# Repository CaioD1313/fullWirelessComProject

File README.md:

# fullWirelessComProject
Schematics, PCB, Firmwares, DataSheets, Notes and Documentation of this project.

# Full Wireless Communication Device

This project was developed as part of the interview process for the Firmware Engineer position. The objective was to build a Full Wireless Communication Device capable of sending data over a 100m air gap. The repository contains the following components in the main folder/root directory:

- **Datasheets**: This folder contains the datasheets used for the development of the project.
- **Schematics and PCB files**: The "KiCad Projeto Tractian" folder includes the schematics and PCB files related to the project.
- **Firmware**: The "Firmware_fullWirelessSystem" folder contains the firmware code for the device.
- **Technical Documentation**: The project's complete technical documentation can be found in the root directory as the file "Project's Technical Documentation.pdf".

Feel free to explore the respective folders for more details on each aspect of the project.

**Be aware! The documentation is long and tedious, as every technical document should be. (:**

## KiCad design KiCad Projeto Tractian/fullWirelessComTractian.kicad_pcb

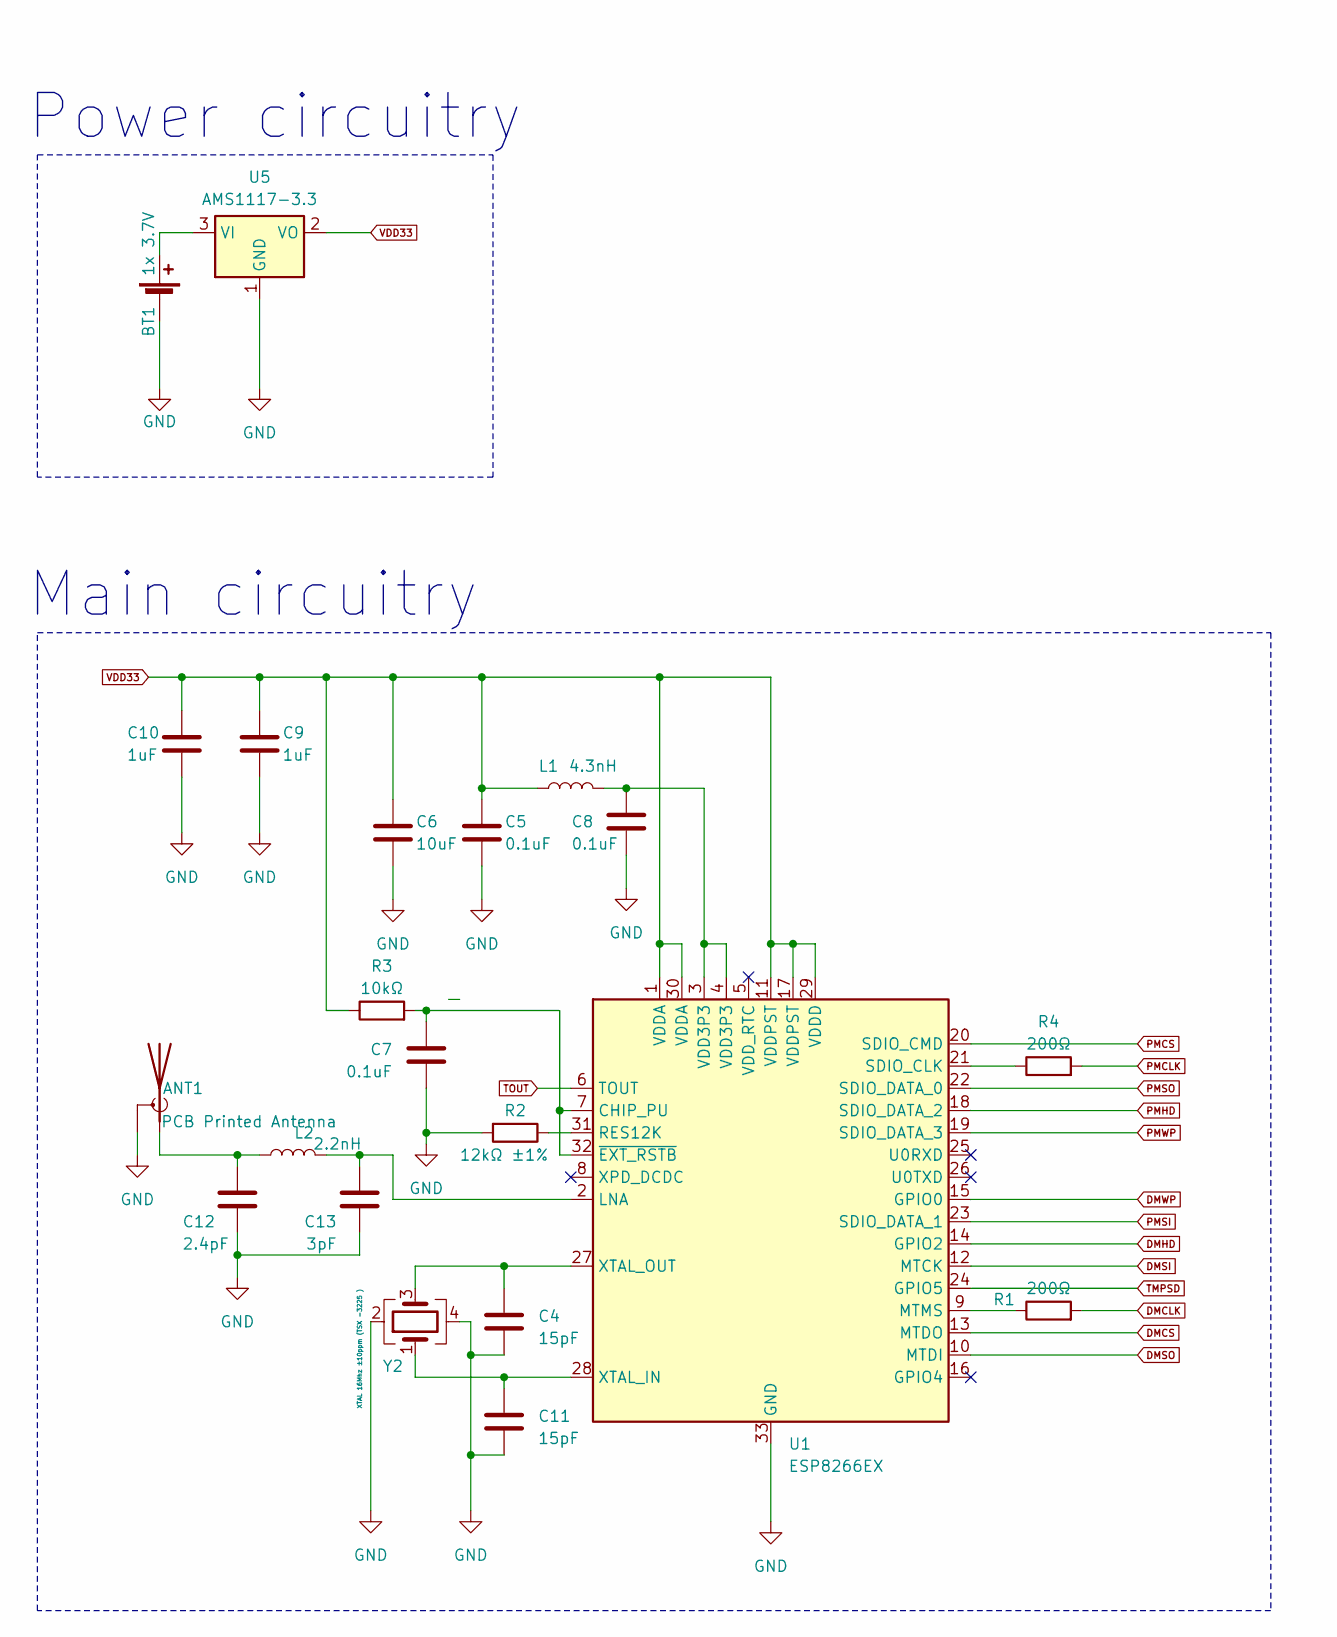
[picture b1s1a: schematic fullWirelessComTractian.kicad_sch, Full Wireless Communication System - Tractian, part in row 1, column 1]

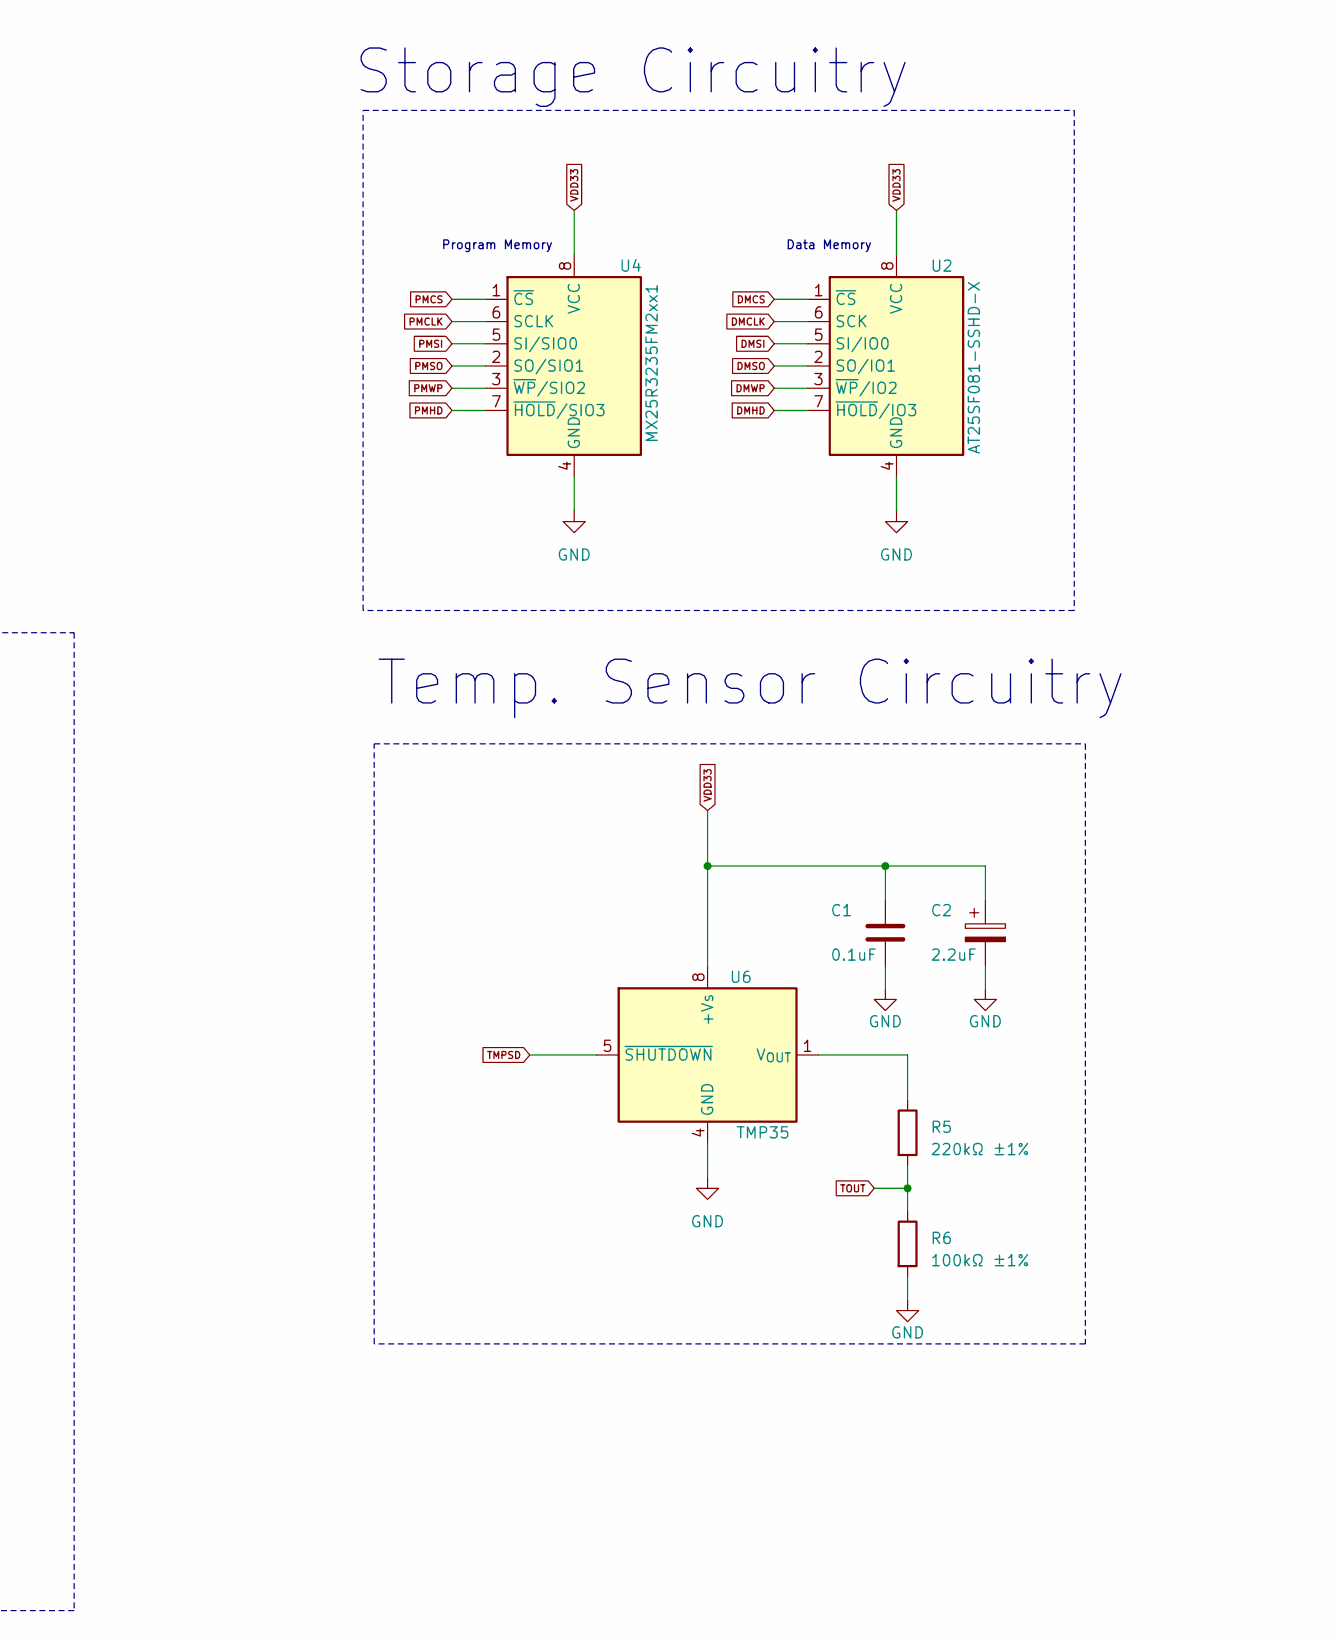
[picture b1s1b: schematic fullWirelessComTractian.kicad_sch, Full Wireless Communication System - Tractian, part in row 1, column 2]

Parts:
ANT1: PCB Printed Antenna; Texas_SWRA117D_2.4GHz_Left
BT1: 1x 3.7V; BatteryHolder_Keystone_2466_1xAAA
C1, C5, C7, C8: 0.1uF; C_0201_0603Metric_Pad0.64x0.40mm_HandSolder
C2: 2.2uF; CP_EIA-1608-08_AVX-J_Pad1.25x1.05mm_HandSolder
C4, C11: 15pF; C_0201_0603Metric_Pad0.64x0.40mm_HandSolder
C6: 10uF; C_0201_0603Metric_Pad0.64x0.40mm_HandSolder
C9, C10: 1uF; C_0201_0603Metric_Pad0.64x0.40mm_HandSolder
C12: 2.4pF; C_0201_0603Metric_Pad0.64x0.40mm_HandSolder
C13: 3pF; C_0201_0603Metric_Pad0.64x0.40mm_HandSolder
L1: 4.3nH; L_0603_1608Metric_Pad1.05x0.95mm_HandSolder
L2: 2.2nH; L_0603_1608Metric_Pad1.05x0.95mm_HandSolder
R1, R4: 200Ω; R_0402_1005Metric_Pad0.72x0.64mm_HandSolder
R2: 12kΩ ±1%; R_0201_0603Metric_Pad0.64x0.40mm_HandSolder
R3: 10kΩ; R_0201_0603Metric_Pad0.64x0.40mm_HandSolder
R5: 220kΩ ±1%; R_0201_0603Metric_Pad0.64x0.40mm_HandSolder
R6: 100kΩ ±1%; R_0201_0603Metric_Pad0.64x0.40mm_HandSolder
U1: ESP8266EX; QFN-32-1EP_5x5mm_P0.5mm_EP3.45x3.45mm
U2: AT25SF081-SSHD-X; SOIC-8_3.9x4.9mm_P1.27mm
U4: MX25R3235FM2xx1; SOP-8_5.28x5.23mm_P1.27mm
U5: AMS1117-3.3; SOT-223-3_TabPin2
U6: TMP35; SOIC-8_3.9x4.9mm_P1.27mm
Y2: XTAL 16Mhz ±10ppm (TSX -3225 ); Oscillator_SMD_SeikoEpson_SG210-4Pin_2.5x2.0mm_HandSoldering

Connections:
DMCLK: R1.2, U2.6 (SCK)
DMCS: U1.13 (MTDO), U2.1 (~CS)
DMHD: U1.14 (GPIO2), U2.7 (~HOLD/IO3)
DMSI: U1.12 (MTCK), U2.5 (SI/IO0)
DMSO: U1.10 (MTDI), U2.2 (SO/IO1)
DMWP: U1.15 (GPIO0), U2.3 (~WP/IO2)
GND: ANT1.2 (Shield), BT1.2 (-), C1.2, C2.2, C4.2, C5.2, C6.2, C7.2, C8.2, C9.2, C10.2, C11.2, C12.2, C13.2, R2.2, R6.2, U1.33 (GND), U2.4 (GND), U4.4 (GND), U5.1 (GND), U6.4 (GND), Y2.2, Y2.4
unnamed: ANT1.1 (A), C12.1, L2.1
unnamed: BT1.1 (+), U5.3 (VI)
unnamed: C8.1, L1.2, U1.3 (VDD3P3), U1.4 (VDD3P3)
unnamed: C7.1, R3.2, U1.7 (CHIP_PU), U1.32 (~EXT_RSTB)
unnamed: C13.1, L2.2, U1.2 (LNA)
unnamed: R1.1, U1.9 (MTMS)
unnamed: R2.1, U1.31 (RES12K)
unnamed: R4.1, U1.21 (SDIO_CLK)
unnamed: C11.1, U1.28 (XTAL_IN), Y2.1
unnamed: C4.1, U1.27 (XTAL_OUT), Y2.3
unnamed: R5.1, U6.1 (V_{OUT})
PMCLK: R4.2, U4.6 (SCLK)
PMCS: U1.20 (SDIO_CMD), U4.1 (~CS)
PMHD: U1.18 (SDIO_DATA_2), U4.7 (~HOLD/SIO3)
PMSI: U1.23 (SDIO_DATA_1), U4.5 (SI/SIO0)
PMSO: U1.22 (SDIO_DATA_0), U4.2 (SO/SIO1)
PMWP: U1.19 (SDIO_DATA_3), U4.3 (~WP/SIO2)
TMPSD: U1.24 (GPIO5), U6.5 (~SHUTDOWN)
TOUT: R5.2, R6.1, U1.6 (TOUT)
VDD33: C1.1, C2.1, C5.1, C6.1, C9.1, C10.1, L1.1, R3.1, U1.1 (VDDA), U1.11 (VDDPST), U1.17 (VDDPST), U1.29 (VDDD), U1.30 (VDDA), U2.8 (VCC), U4.8 (VCC), U5.2 (VO), U6.8 (+Vs)

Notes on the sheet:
Temp. Sensor Circuitry
Storage Circuitry
Program Memory
Data Memory
Main circuitry
Power circuitry

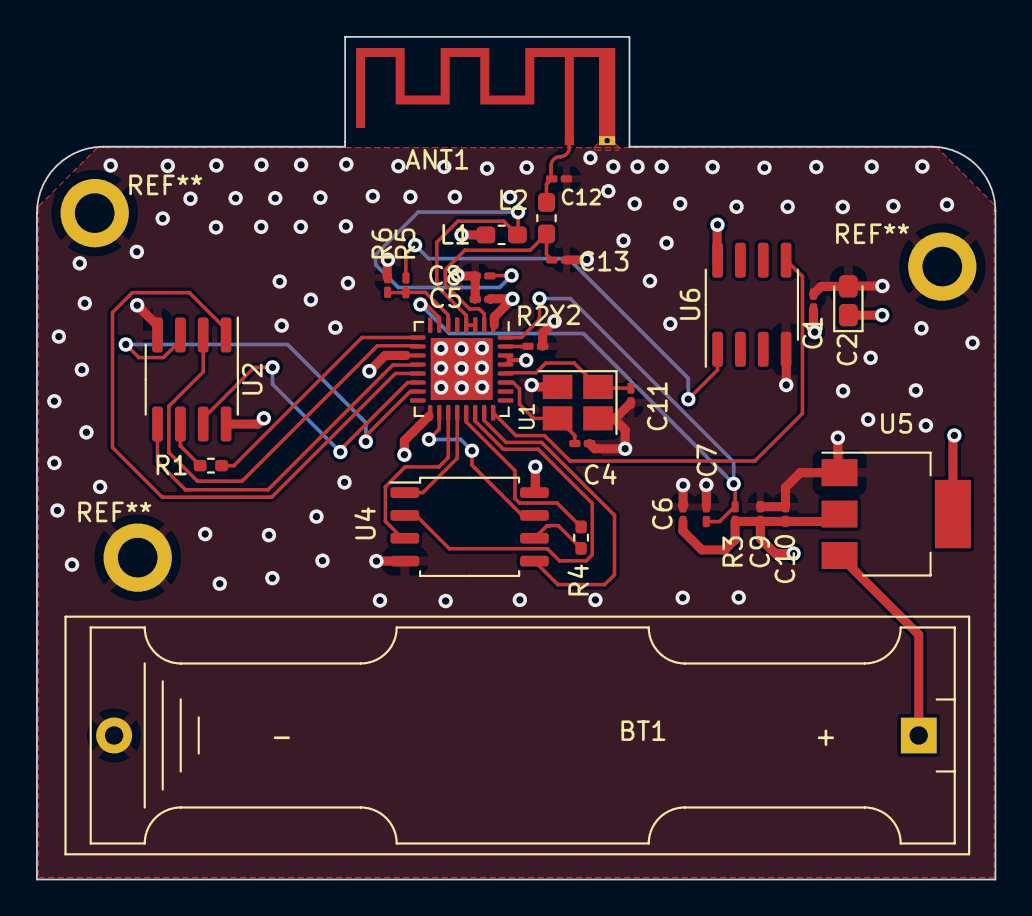
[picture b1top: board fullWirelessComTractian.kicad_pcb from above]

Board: 4 copper layers, 53.3 x 46.8 mm, 28 parts (0 on the bottom side), 27 nets.

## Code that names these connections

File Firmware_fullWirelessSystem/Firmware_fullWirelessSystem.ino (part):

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*/

// Data Memory GPIO's definitions for SPI comm:
#define DMCS 15 // Data Memory Chip/Slave Select - Pin 13 on ESP8266EX -> (MTDO) GPIO15
#define DMCLK 14 // Data Memory Serial Clock - Pin 9 on ESP8266EX -> (MTMS) GPIO14
#define DMSI 13 // Data Memory SI (slave data input) (MOSI) - Pin 12 on ESP8266EX -> (MTCK) GPIO13
#define DMSO 12 // Data Memory SO (slave data output) (MISO) - Pin 10 on ESP8266EX -> (MTDI) GPIO12
#define DMWP 0 // Data Memory Write Protect - Pin 15 on ESP8266EX -> (GPIO0) GPIO0
#define DMHD 2 // Data Memory Hold - Pin 14 on ESP8266EX -> (GPIO2) GPIO2

// SPI delay for 8Mhz comm (Flash Data Memory operates up to 8Mhz for single IO mode)
// For we are using bit banging data, a (way) lower frequency will be used.
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

// Temperature Sensor GPIO definition
#define Temp_Sensor_ADC_Pin 17 // TMP35 Vout - Pin 6 on ESP8266EX -> (TOUT) ADC_in | On NodeMCU it is mapped to pin 17
#define Temp_Sensor_Shutdown_Pin 5 // TMP35 SHUTDOWN - Pin 24 on ESP8266EX -> (GPIO5) GPIO5



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void setup() {
  
  // defining the 4xIO of the Data Memory SPI and some of its states
  pinMode(DMSO, INPUT); 
  pinMode(DMSI, OUTPUT);
  pinMode(DMCLK, OUTPUT);
  pinMode(DMCS, OUTPUT);
  digitalWrite(DMCS, HIGH); // Set Slave Select to HIGH, so it is guranteed to be inactive
  digitalWrite(DMCLK, LOW); // Gurantees SCLK is set to LOW so when the COM starts the clock is on idle mode

  // defitions of the Hold and WP Pins of Data Memory
  digitalWrite(DMHD, HIGH); // sets the Hold Pin on the Data Memory to HIGH, so its inactive
  digitalWrite(DMWP, HIGH); // sets the Write Protect Pin on the Data Memory to HIGH, so its inactive

  //definition of the SHUTDOWN pin of TMP35
  pinMode(Temp_Sensor_Shutdown_Pin,OUTPUT);
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      digitalWrite(DMSI,LOW);
    }

    digitalWrite(DMCLK, HIGH); // Sets SCK (Clock) to HIGH so the slave reads the DMSI GPIO on rising edge of clock
    delayMicroseconds(Half_SPI_Period); // COM delay
    digitalWrite(DMCLK, LOW); // Sets SCK (Clock) to LOW so the slave sends the kth bit to the master
      
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
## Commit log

2023-05-11 :memo: add restante dos data sheets (Atmega328P-A eh muito grande pra subir)
2023-05-14 1 - :fire: | 2 -:memo: | 1 - Remocao dos circuitos p/ Atmega328P-A e Alimentacao Rede | 2 - Add Data Sheet AMS1117
2023-05-14 :arrow_up: Modificacao da PCB para 4-layers
2023-05-14 :construction: Add GND Mounting Holes and PCB borders
2023-05-14 :construction: Arranjo dos componentes | destaque para o circuito pi e XTAL em 0.8mm
2023-05-14 :construction: Schematics reorganizado | definicao de trail mils para power/GND lines e signal lines
2023-05-15 1 - :boom: | 2 - :memo: | 1- Calculo e projeto da impedancia de 50ohms para a antena RF | 2 - add datasheet antena RTexasSWRA117D 2.4GHz
2023-05-15 :construction: Nova organizacao da PCB | Routing in progress
2023-05-15 :heavy_plus_sign: Add circuito TMP36 Temp Sensor
2023-05-16 :construction: PCB Routes Finished | PCB Borders defined | ANT1 track drawn manually (error ignore on no net connection for ANT1)
2023-05-16 :construction: Add tantos GND vias quanto possível para melhor aterramento - RF design ESP datasheet
2023-05-16 1 - :rocket: | 2 :memo: | 1 - Final PCB and Gerbers | 2 - Add doc TMP36
2023-05-16 :tada: Add do arquivo do firmware - Descricao do Firmware e inicio da subrotina do bit banging SPI -IDE do Arduino
2023-05-16 :rocket: Bit banging SPI subroutine and pre definitions
2023-05-16 :rocket: Read (Page Program) subroutine
2023-05-16 :bug: fix da Read subroutine
2023-05-17 :rocket: Rotina de leitura de temperatura com estabilizacao por filtro LTI media movel
2023-05-17 1 - :rocket: | 2 - :rocket: - 1 - Erase Chip routine | 2 - Temperatue Collect, Write on Data Memory on main loop
2023-05-17 :rocket: Read (right this time) 1024 bytes of data Function
2023-05-17 :rocket: Final version of the firmware (yet to be revised) | Implementation of whole Wifi comm
2023-05-18 :memo: Full LaTeX preparation of project Documentation - Add Doc Folder
2023-05-18 :memo: estrutura da doc ver 1.1
2023-05-18 :memo: Updates on the documentation | Preliminares, Introduction and Part of Schematics and PCB Design
2023-05-19 :memo: Updates on the documentation | Preliminares, Introduction, Schematics and PCB Design completed
2023-05-19 :white_check_mark: Final commit, project completed

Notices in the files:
Firmware_fullWirelessSystem/Firmware_fullWirelessSystem.ino:
For the WiFi protocol, it is used the "ESP8266WiFi.h" library licensed under LGPL (Lesser General
Public License) Version 2.1, which in broad terms it can be interpreted as follows:
"Primarily used for software libraries, the GNU LGPL
requires that derived works be licensed under the same license, but works that only link to it do not
